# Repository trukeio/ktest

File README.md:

# Truke Ktest

Ktest turns a Linux machine and the test equipment connected to it into an
instrument rack you use from a browser. It covers three jobs that are usually
done by three unrelated tools:

- **Bus work.** CAN and CAN FD monitoring, decoding, transmit and replay over
  SocketCAN. LIN, ISO-TP and J1939 are planned.
- **Bench work.** Programmable supplies and oscilloscopes over SCPI. DMMs,
  loads and function generators are planned.
- **Recording.** Everything above goes onto one timeline, in one open format,
  [Logb](https://github.com/rveen/logb).

Having all three in one place is the reason the project exists. Bus tools do not
see the bench, and bench software does not see the bus, so today a supply
transient and the CAN traffic it caused have to be matched up by hand.

Ktest is meant as an open alternative to proprietary test environments such as
Vector CANoe. It is MIT licensed, and it keeps your test data in an open format.

<p>

</p>

## How it works

```
  browser (any OS)
      |  REST (control)     HTTP chunked response (Logb stream)
      v                                  ^
  +---------------------------------------------------+
  |  ktestd (Go, Linux)                               |
  |  bus layer      instrument layer   ->  .logb file |
  +---------------------------------------------------+
      |                    |
   CAN interfaces     bench instruments
```

- **The daemon owns the hardware.** It keeps connections open and leases
  sessions, and a run continues if the browser disconnects.
- **Everything produced is a Logb stream.** The file on disk and the bytes on
  the wire use the same format, so the live view and replay share one decoder.
- **Control goes one way.** Commands go in over REST, and results come back only
  on the stream. Nothing is actuated by default: a client must take a lease and
  arm the rack first, and every action is checked against limits that are
  written into the recording.
- **Timing is handled below the daemon.** The kernel runs cyclic transmit
  (CAN_BCM), not the daemon's event loop.

The full design is in [doc/test-software-outline.md](doc/test-software-outline.md).

## Commands

| Command | What it does |
| --- | --- |
| `cmd/ktestd` | The rack daemon. Records a bus, drives supplies and scopes, and serves the browser UI over HTTPS. |
| `cmd/canlogb` | A small CAN recorder: SocketCAN in, Logb out. It has no control plane, so it cannot actuate anything. |
| `cmd/logbcheck` | Checks a recording against independent references, such as candump logs and simulator transcripts. It also checks every control decision against the declared limits. |
| `cmd/psusim` | A simulated two-channel bench supply (Keysight SCPI dialect) with a resistive load on each channel. |
| `cmd/scopesim` | A simulated oscilloscope (Siglent SDS1000X-E SCPI dialect). |
| `cmd/vcanprobe` | Measures what a SocketCAN interface can actually do (timestamping, pacing, overflow). |

The Go packages are `can/` (SocketCAN), `record/` (frames to Logb), `stream/`
(fanning out a Logb stream to many consumers), `psu/` and `scope/`
(instrument drivers and simulators). The browser UI is in `web/`. It is written
in TypeScript, and its built output in `web/dist/` is committed and embedded in
`ktestd`.

## Getting started

The [user manual](https://trukeio.github.io/ktest/) ([source](doc/manual.html)) covers building and installing, setting up a
bench, the rack, scripting, limits and access in full. What follows is the
short version.

You need Linux and Go 1.25 or newer. The CAN and recording code uses AF_CAN
directly, so it only builds on Linux.

`go.mod` uses a `replace` directive that expects Logb to be checked out next to
this repository:

```sh
git clone https://github.com/rveen/logb ../logb
go build ./...
go test ./...
```

Without hardware, use a virtual CAN interface:

```sh
sudo modprobe vcan
sudo ip link add dev vcan0 type vcan
sudo ip link set up vcan0
```

Then run one of the demos. Each demo uses a simulated instrument, so no
hardware is needed:

- [examples/supply-bench](examples/supply-bench/README.md) drives a simulated
  bench supply at `https://localhost:8443/`.
- [examples/scope-bench](examples/scope-bench/README.md) drives a simulated
  oscilloscope at `https://localhost:8444/`.

```sh
examples/supply-bench/demo.sh
```

The demo prints a login token. Open the URL, accept the self-signed certificate
and paste the token.

For real hardware, [examples/orangepi-zero2-mcp2518fd](examples/orangepi-zero2-mcp2518fd/README.md)
describes a CAN FD interface on an Orange Pi Zero 2.

## Rebuilding the web UI

You only need to do this if you change `web/src/`:

```sh
cd web
npm install
npm run build
npm test
```

## Status

This is early, active work. Milestones 1 to 3 of the design outline are built.
Interfaces, file layouts and flags may still change.

## License

MIT, see [LICENSE](LICENSE).

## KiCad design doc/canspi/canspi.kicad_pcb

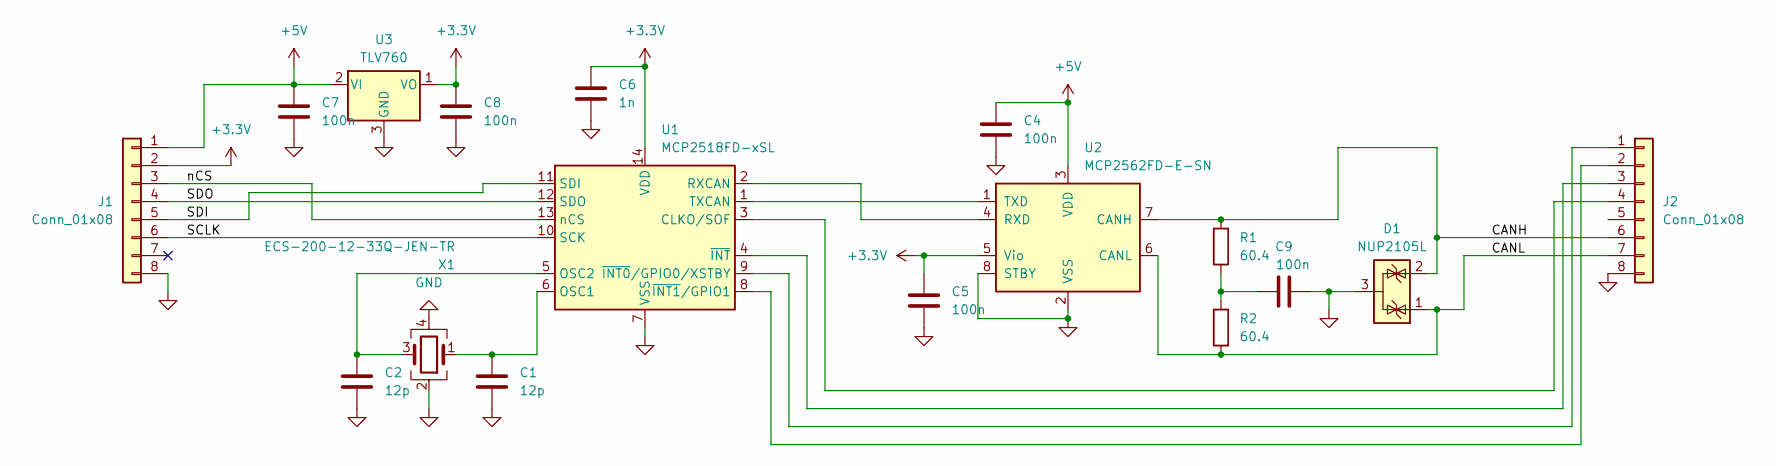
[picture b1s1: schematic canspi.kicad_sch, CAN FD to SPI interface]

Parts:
C1, C2: 12p; C_0603_1608Metric_Pad1.08x0.95mm_HandSolder
C4, C5, C7, C8, C9: 100n; C_0603_1608Metric_Pad1.08x0.95mm_HandSolder
C6: 1n; C_0603_1608Metric_Pad1.08x0.95mm_HandSolder
D1: NUP2105L; SOT-23
J1, J2: Conn_01x08; PinHeader_1x08_P2.54mm_Vertical
R1, R2: 60.4; R_1206_3216Metric_Pad1.30x1.75mm_HandSolder
U1: MCP2518FD-xSL; SOIC-14_3.9x8.7mm_P1.27mm
U2: MCP2562FD-E-SN; SOIC-8_3.9x4.9mm_P1.27mm
U3: TLV760; SOT-23
X1: ECS-200-12-33Q-JEN-TR; Crystal_SMD_3225-4Pin_3.2x2.5mm_HandSoldering

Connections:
+3.3V: C5.1, C6.1, C8.1, J1.2, U1.14 (VDD), U2.5 (Vio), U3.1 (VO)
+5V: C4.1, C7.1, J1.1, U2.3 (VDD), U3.2 (VI)
/CANH: D1.2 (K), J2.6, R1.2, U2.7 (CANH)
/CANL: D1.1 (K), J2.7, R2.1, U2.6 (CANL)
/SCLK: J1.6, U1.10 (SCK)
/SDI: J1.5, U1.11 (SDI)
/SDO: J1.4, U1.12 (SDO)
/nCS: J1.3, U1.13 (nCS)
GND: C1.2, C2.2, C4.2, C5.2, C6.2, C7.2, C8.2, C9.2, D1.3 (A), J1.8, J2.8, U1.7 (VSS), U2.2 (VSS), U2.8 (STBY), U3.3 (GND), X1.2, X1.4
unnamed: C9.1, R1.1, R2.2
unnamed: J2.1, U1.9 (~INT0/GPIO0/XSTBY)
unnamed: J2.2, U1.8 (~INT1/GPIO1)
unnamed: J2.3, U1.4 (~INT)
unnamed: J2.4, U1.3 (CLKO/SOF)
unnamed: C1.1, U1.6 (OSC1), X1.1
unnamed: C2.1, U1.5 (OSC2), X1.3
unnamed: U1.2 (RXCAN), U2.4 (RXD)
unnamed: U1.1 (TXCAN), U2.1 (TXD)

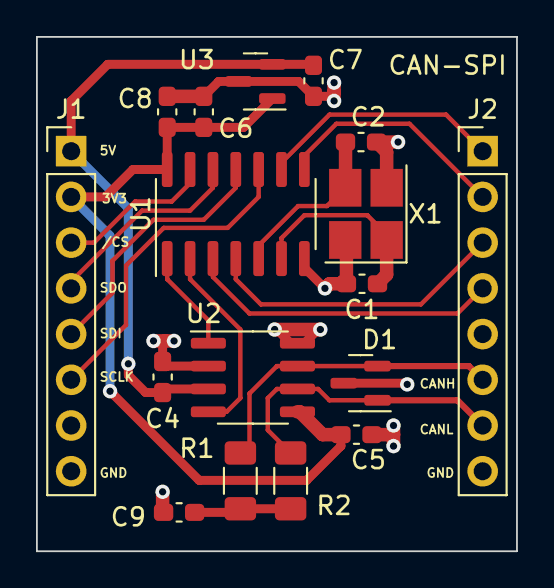
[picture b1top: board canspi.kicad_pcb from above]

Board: 2 copper layers, 26.7 x 28.6 mm, 17 parts (0 on the bottom side), 18 nets.
